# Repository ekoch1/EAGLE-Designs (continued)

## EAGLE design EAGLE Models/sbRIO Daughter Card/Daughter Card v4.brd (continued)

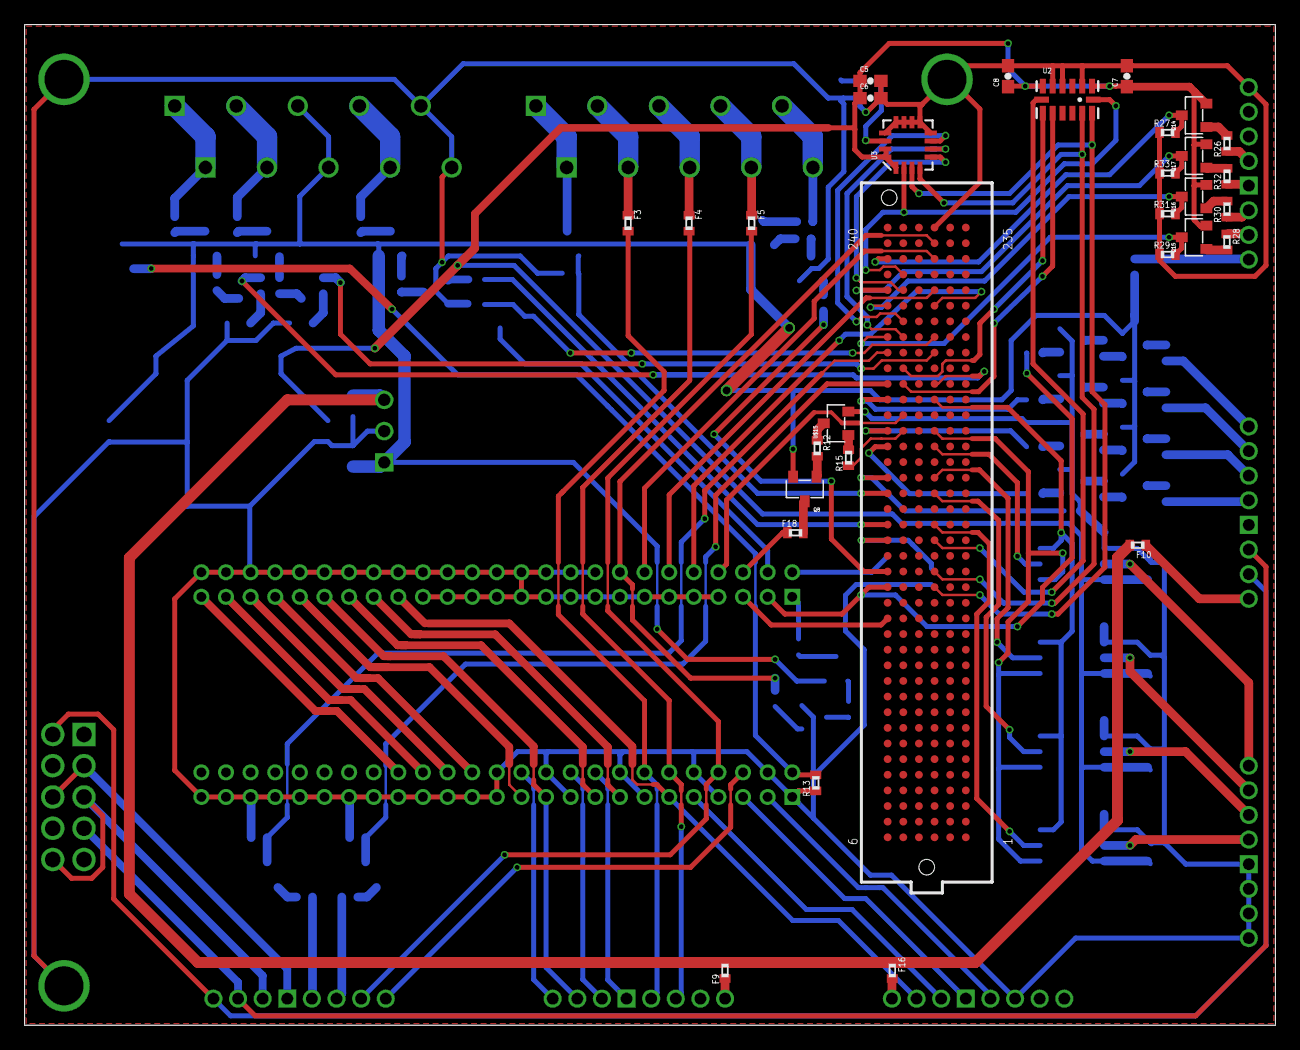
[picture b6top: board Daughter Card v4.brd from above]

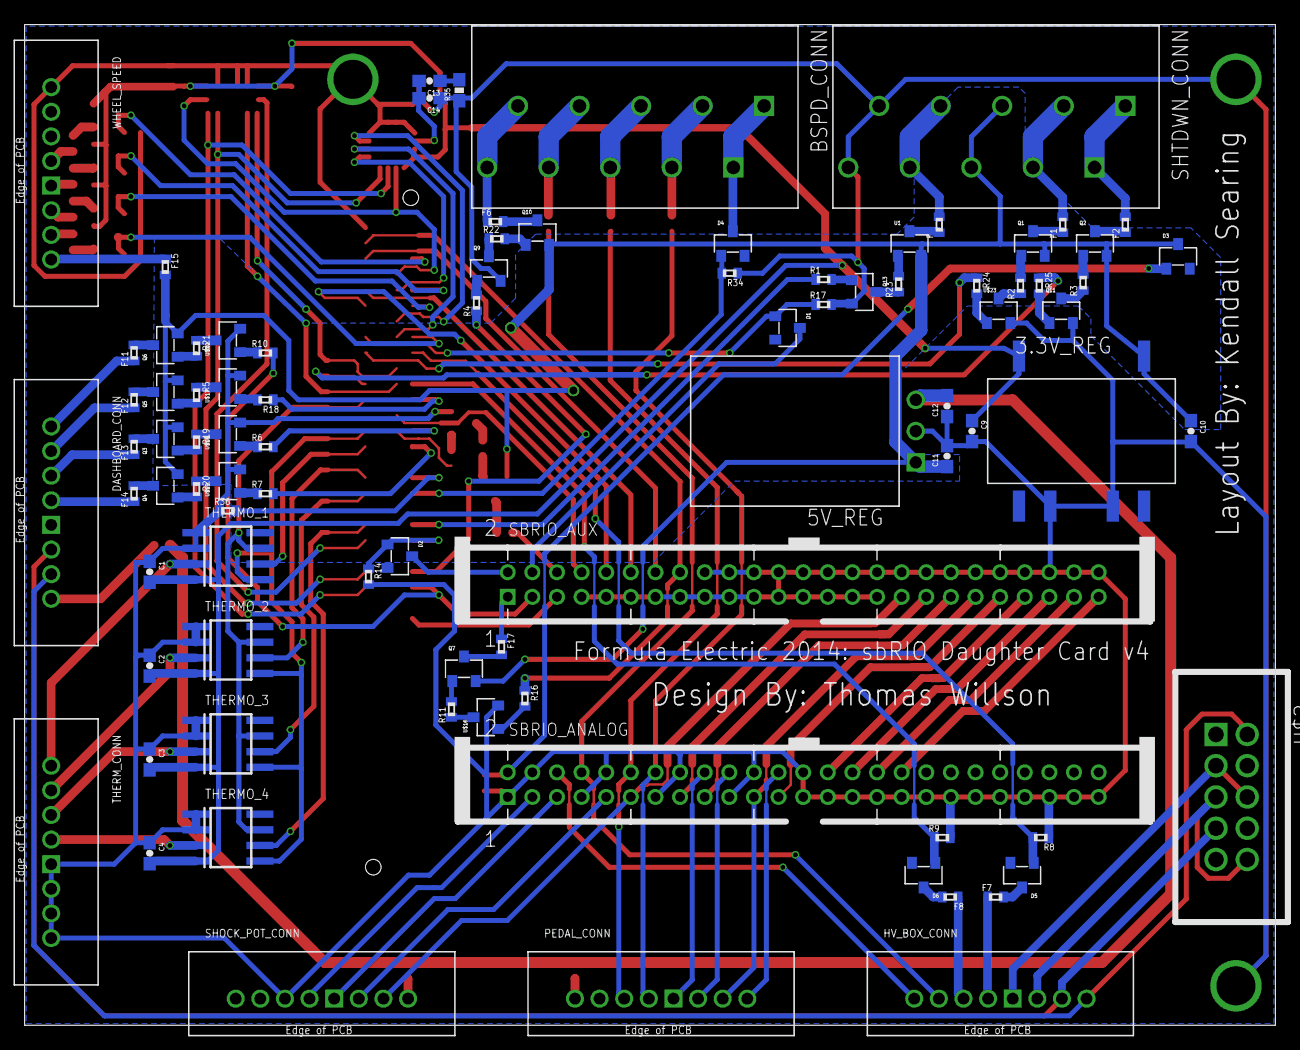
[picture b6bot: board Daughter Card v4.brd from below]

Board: 2 copper layers, 101.6 x 81.3 mm, 119 parts (88 on the bottom side), 146 nets.

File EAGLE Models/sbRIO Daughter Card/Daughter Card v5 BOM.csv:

"Part";"Value";"Device";"Package";"Description";"MF";"MPN";"OC_FARNELL";"OC_NEWARK";
"3.3V_REG";"V7803-1000";"V7803-1000";"V78XX-1000";"";"";"";"";"";
"5V_REG";"V78XX-1500";"V78XX-1500";"V78XX-1500R";"";"";"";"";"";
"ACCUMULATOR_CONN";"RJ45-6L21-S";"RJ45-6L21-S";"RJ45-SHIELD1";"RJ45 Low Profile Shield Type 2";"";"";"unknown";"unknown";
"AIO_PO_CONN";"2516-5";"2516-5";"PAK100/2500-5-16";"3M (TM) Pak 100 4-Wall Header";"";"D2516-5002-AR";"9838376";"12P7055";
"BSPD_CONN";"CONN_5";"CONN_5";"CONNECTOR_5";"";"";"";"";"";
"C5";".1uF";"CAP0603-CAP";"0603-CAP";"Capacitor";"";"";"";"";
"C6";"10uF";"CAP0603-CAP";"0603-CAP";"Capacitor";"";"";"";"";
"C7";".1uF";"CAP0603-CAP";"0603-CAP";"Capacitor";"";"";"";"";
"C8";"1uF";"CAP0603-CAP";"0603-CAP";"Capacitor";"";"";"";"";
"C9";"22uF";"CAP0603-CAP";"0603-CAP";"Capacitor";"";"";"";"";
"C10";"10uF";"CAP0603-CAP";"0603-CAP";"Capacitor";"";"";"";"";
"C11";"10uF";"CAP0603-CAP";"0603-CAP";"Capacitor";"";"";"";"";
"C12";"22uF";"CAP0603-CAP";"0603-CAP";"Capacitor";"";"";"";"";
"C13";"470nF";"CAP0603-CAP";"0603-CAP";"Capacitor";"";"";"";"";
"C14";"10nF";"CAP0603-CAP";"0603-CAP";"Capacitor";"";"";"";"";
"D1";"MMBZ5238B-7-F";"MMBZ5238B-7-F";"SOT-23-3";"Digikey: MMBZ5238B-FDICT-ND";"";"";"";"";
"D2";"MMBZ5238B-7-F";"MMBZ5238B-7-F";"SOT-23-3";"Digikey: MMBZ5238B-FDICT-ND";"";"";"";"";
"D3";"MMBZ5238B-7-F";"MMBZ5238B-7-F";"SOT-23-3";"Digikey: MMBZ5238B-FDICT-ND";"";"";"";"";
"D4";"MMBZ5238B-7-F";"MMBZ5238B-7-F";"SOT-23-3";"Digikey: MMBZ5238B-FDICT-ND";"";"";"";"";
"D5";"MMBZ5238B-7-F";"MMBZ5238B-7-F";"SOT-23-3";"Digikey: MMBZ5238B-FDICT-ND";"";"";"";"";
"D6";"MMBZ5238B-7-F";"MMBZ5238B-7-F";"SOT-23-3";"Digikey: MMBZ5238B-FDICT-ND";"";"";"";"";
"F1";"";"R-EU_R0402";"R0402";"RESISTOR, European symbol";"";"";"";"";
"F2";"";"R-EU_R0402";"R0402";"RESISTOR, European symbol";"";"";"";"";
"F3";"";"R-EU_R0402";"R0402";"RESISTOR, European symbol";"";"";"";"";
"F4";"";"R-EU_R0402";"R0402";"RESISTOR, European symbol";"";"";"";"";
"F5";"";"R-EU_R0402";"R0402";"RESISTOR, European symbol";"";"";"";"";
"F6";"";"R-EU_R0402";"R0402";"RESISTOR, European symbol";"";"";"";"";
"F7";"";"R-EU_R0402";"R0402";"RESISTOR, European symbol";"";"";"";"";
"F8";"";"R-EU_R0402";"R0402";"RESISTOR, European symbol";"";"";"";"";
"F9";"";"R-EU_R0402";"R0402";"RESISTOR, European symbol";"";"";"";"";
"F10";"";"R-EU_R0402";"R0402";"RESISTOR, European symbol";"";"";"";"";
"F14";"";"R-EU_R0402";"R0402";"RESISTOR, European symbol";"";"";"";"";
"F15";"";"R-EU_R0402";"R0402";"RESISTOR, European symbol";"";"";"";"";
"F16";"";"R-EU_R0402";"R0402";"RESISTOR, European symbol";"";"";"";"";
"F17";"";"R-EU_R0402";"R0402";"RESISTOR, European symbol";"";"";"";"";
"F18";"";"R-EU_R0402";"R0402";"RESISTOR, European symbol";"";"";"";"";
"F19";"";"R-EU_R0402";"R0402";"RESISTOR, European symbol";"";"";"";"";
"F20";"";"R-EU_R0402";"R0402";"RESISTOR, European symbol";"";"";"";"";
"F21";"";"R-EU_R0402";"R0402";"RESISTOR, European symbol";"";"";"";"";
"F22";"";"R-EU_R0402";"R0402";"RESISTOR, European symbol";"";"";"";"";
"IC1";"BTS716G";"BTS716G";"PG-DSO-20";"Smart High-Side Power Switch Four Channels: 4 x 140mOhm staus Feedback";"";"";"unknown";"unknown";
"IC2";"BTS716G";"BTS716G";"PG-DSO-20";"Smart High-Side Power Switch Four Channels: 4 x 140mOhm staus Feedback";"";"";"unknown";"unknown";
"IC3";"BTS716G";"BTS716G";"PG-DSO-20";"Smart High-Side Power Switch Four Channels: 4 x 140mOhm staus Feedback";"";"";"unknown";"unknown";
"Q7";"MMBT4403-7-F";"MMBT4403-7-F";"SOT-23-3";"";"";"";"";"";
"Q8";"MMBT4403-7-F";"MMBT4403-7-F";"SOT-23-3";"";"";"";"";"";
"R8";"10k";"R-US_R0402";"R0402";"RESISTOR, American symbol";"";"";"";"";
"R9";"10k";"R-US_R0402";"R0402";"RESISTOR, American symbol";"";"";"";"";
"R11";"4.7k";"R-US_R0402";"R0402";"RESISTOR, American symbol";"";"";"";"";
"R12";"4.7k";"R-US_R0402";"R0402";"RESISTOR, American symbol";"";"";"";"";
"R13";"10k";"R-US_R0402";"R0402";"RESISTOR, American symbol";"";"";"";"";
"R14";"10k";"R-US_R0402";"R0402";"RESISTOR, American symbol";"";"";"";"";
"R15";"4.7k";"R-US_R0402";"R0402";"RESISTOR, American symbol";"";"";"";"";
"R16";"4.7k";"R-US_R0402";"R0402";"RESISTOR, American symbol";"";"";"";"";
"R17";"10k";"R-US_R0402";"R0402";"RESISTOR, American symbol";"";"";"";"";
"R34";"10k";"R-US_R0402";"R0402";"RESISTOR, American symbol";"";"";"";"";
"R35";"10K";"RESISTOR0603-RES";"0603-RES";"Resistor";"";"";"";"";
"R36";"10k";"R-US_R0402";"R0402";"RESISTOR, American symbol";"";"";"";"";
"SBRIO_ANALOG";"SBRIO_MIO";"SBRIO_MIO";"SBRIO_J502_J503";"";"";"";"";"";
"SBRIO_AUX";"SBRIO_AUX";"SBRIO_AUX";"SBRIO_J502_J503";"An output for a lot of the extra pins on the sbRIO.";"";"";"";"";
"SHTDWN_CONN";"CONN_5";"CONN_5";"CONNECTOR_5";"";"";"";"";"";
"TUB_CONN";"2516-5";"2516-5";"PAK100/2500-5-16";"3M (TM) Pak 100 4-Wall Header";"";"D2516-5002-AR";"9838376";"12P7055";
"U$2";"SBRIO_W500";"SBRIO_W500";"SBRIO_W";"";"";"";"";"";
"U$3";"SBRIO_RMC";"SBRIO_RMC";"SEAM-40-XX.X-XX-06-X-A";"";"";"";"";"";
"U$15";"MMBT4401-7-F";"MMBT4401-7-F";"SOT-23-3";"";"";"";"";"";
"U$16";"MMBT4401-7-F";"MMBT4401-7-F";"SOT-23-3";"";"";"";"";"";
"U1";"";"TXB0104PWR";"TSSOP14";"4-Bit Bi-Directional Level Shifter";"";"";"";"";
"U2";"ADXL345";"ADXL345";"LGA14";"3-axis SPI/I2C 2/4/8/16g accelerometer";"";"";"";"";
"U3";"L3G4200D";"L3G4200D";"LGA16-4X4";"L3G4200D Three-axis, digital output gyroscope";"";"";"";"";
"X1";"5566-2";"5566-2";"5566-2";"Mini FIT connector 2 pol";"";"";"1822072";"unknown";
"X2";"";"FTOP-4";"FTOP-4";"AMP connector";"";"";"";"";

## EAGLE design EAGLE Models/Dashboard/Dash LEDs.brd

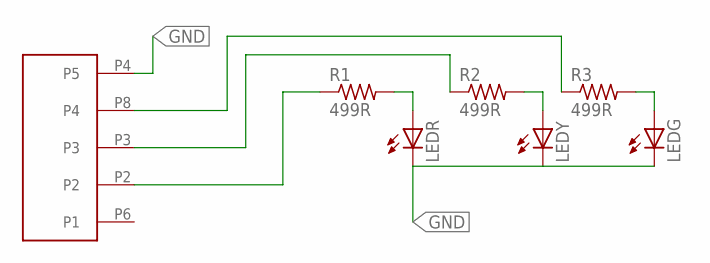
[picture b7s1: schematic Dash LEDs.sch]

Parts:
LEDG: LED5MM
LEDR: LED5MM
LEDY: LED5MM
R1, R2, R3: 499R; R0805
U$1: PICOLOCK

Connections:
DRV1: R1.1, U$1.P2
DRV2: R2.1, U$1.P3
DRV3: R3.1, U$1.P8 (P4)
GND: LEDG.K (C), LEDR.K (C), LEDY.K (C), U$1.P4 (P5)
unnamed: LEDR.A, R1.2
unnamed: LEDY.A, R2.2
unnamed: LEDG.A, R3.2

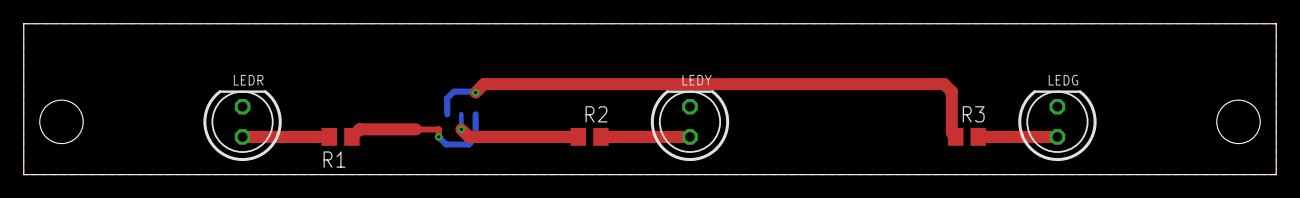
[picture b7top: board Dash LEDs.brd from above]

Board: 2 copper layers, 105.4 x 12.7 mm, 7 parts (1 on the bottom side), 7 nets.

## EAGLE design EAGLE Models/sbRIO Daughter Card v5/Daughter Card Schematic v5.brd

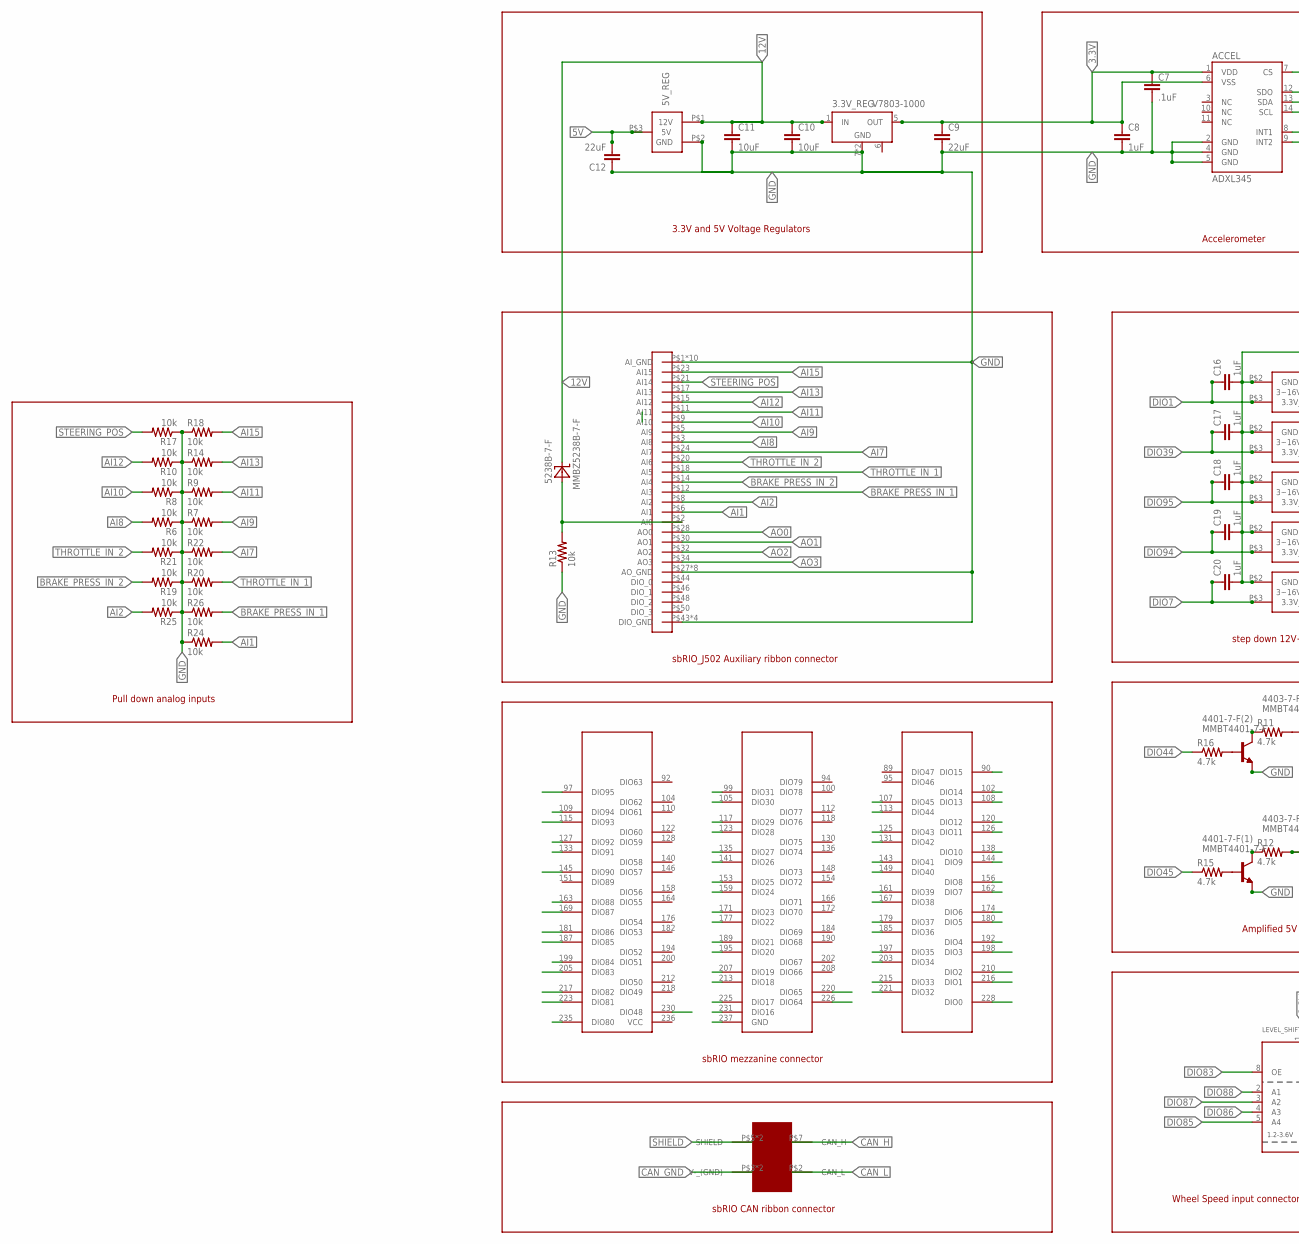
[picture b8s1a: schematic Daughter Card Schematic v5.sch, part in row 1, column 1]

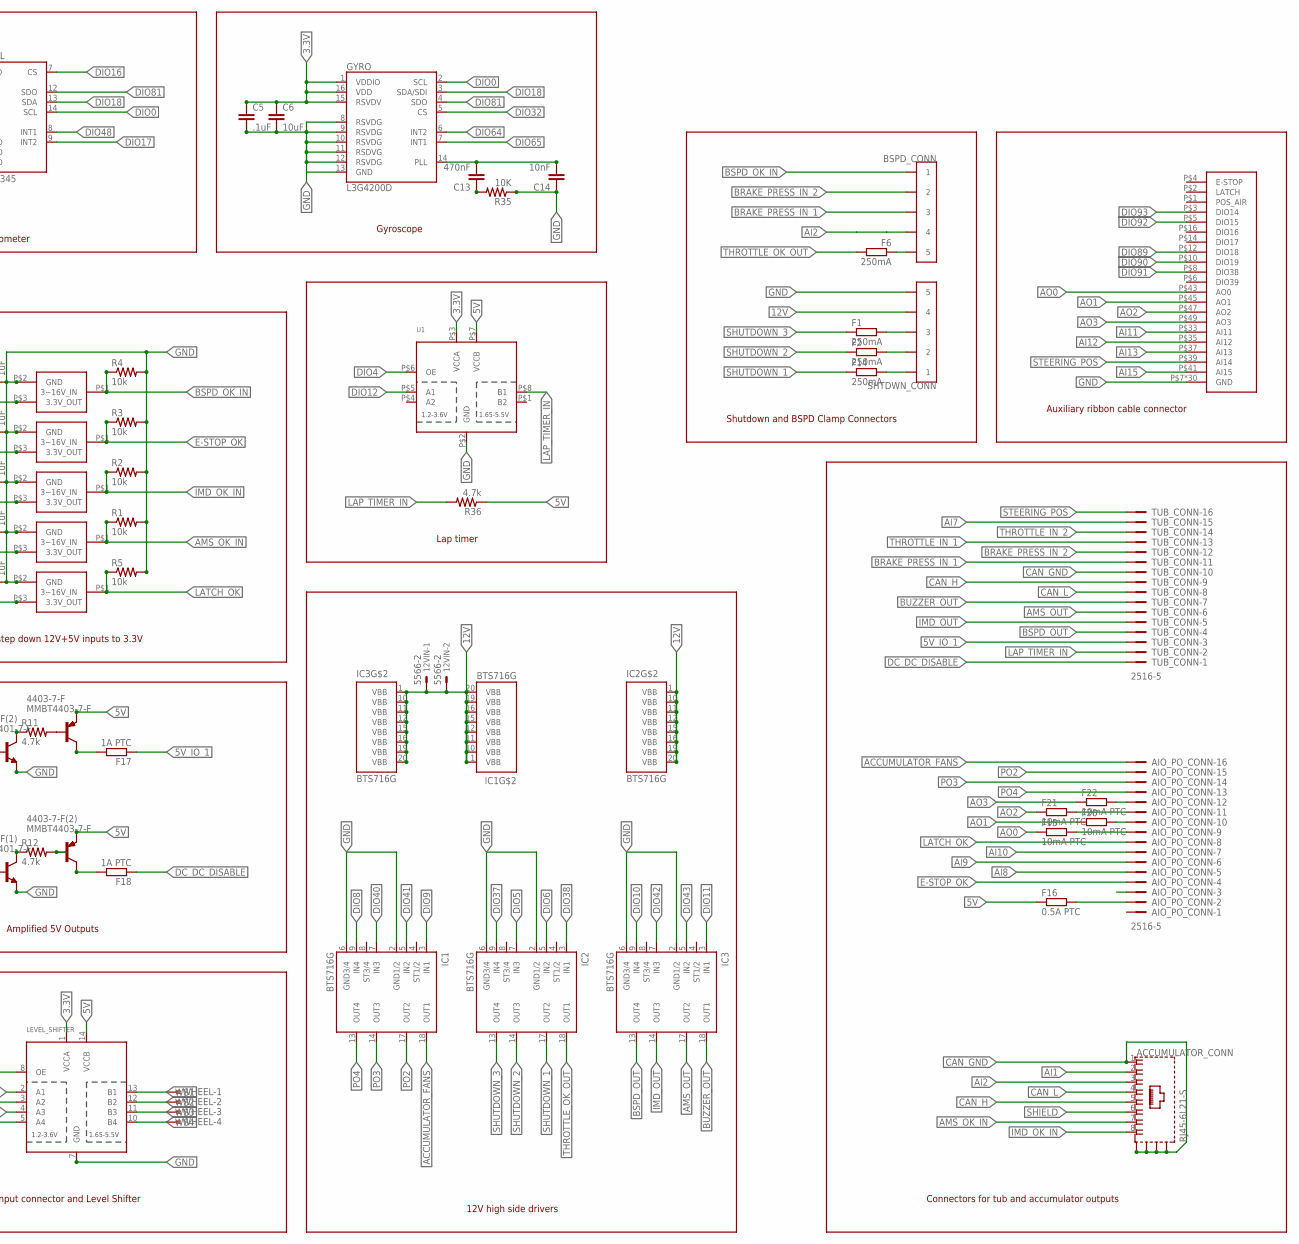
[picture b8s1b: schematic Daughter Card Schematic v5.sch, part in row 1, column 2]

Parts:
3.3V_REG: V7803-1000; V78XX-1000
5V_REG: V78XX-1500; V78XX-1500R
12VIN: 5566-2
4401-7-F(1), 4401-7-F(2): MMBT4401-7-F; SOT-23-3
4403-7-F, 4403-7-F(2): MMBT4403-7-F; SOT-23-3
5225-3.3M5-TR(5), 5525-3.3YM5-TR(1), 5525-3.3YM5-TR(2), 5525-3.3YM5-TR(3), 5525-3.3YM5-TR(4): MIC5225-3.3YM5-TR; SOT-23-3
5238B-7-F: MMBZ5238B-7-F; SOT-23-3
ACCEL: ADXL345; LGA14
ACCUMULATOR_CONN: RJ45-6L21-S; RJ45-SHIELD1
AIO_PO_CONN: 2516-5; PAK100/2500-5-16
BSPD_CONN: CONN_5; CONNECTOR_5
C5, C7: .1uF; 0603-CAP
C6, C10, C11: 10uF; 0603-CAP
C8, C16, C17, C18, C19, C20: 1uF; 0603-CAP
C9, C12: 22uF; 0603-CAP
C13: 470nF; 0603-CAP
C14: 10nF; 0603-CAP
F1, F2, F6, F14: 250mA; R0603
F15, F20, F21, F22: 10mA PTC; R0402
F16: 0.5A PTC; R0603
F17, F18: 1A PTC; R0603
GYRO: L3G4200D; LGA16-4X4
IC1, IC2, IC3: BTS716G; PG-DSO-20
LEVEL_SHIFTER: TXB0104PWR; TSSOP14
R1, R2, R3, R4, R5, R6, R7, R8, R9, R10, R13, R14, R17, R18, R19, R20, R21, R22, R24, R25, R26: 10k; R0402
R11, R12, R15, R16, R36: 4.7k; R0402
R35: 10K; 0603-RES
SBRIO_ANALOG: SBRIO_MIO; SBRIO_J502_J503
SBRIO_AUX: SBRIO_AUX; SBRIO_J502_J503
SBRIO_CAN: SBRIO_W500; SBRIO_W
SBRIO_MEZZANINE: SBRIO_RMC; SEAM-40-XX.X-XX-06-X-A
SHTDWN_CONN: CONN_5; CONNECTOR_5
TUB_CONN: 2516-5; PAK100/2500-5-16
U1: TXS0102; VFSOP-8
WHEEL: FTOP-4

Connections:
3.3V: 3.3V_REG.5 (OUT), ACCEL.1 (VDD), ACCEL.6 (VSS), C5.1, C6.1, C7.1, C8.1, C9.1, GYRO.1 (VDDIO), GYRO.15 (RSVDV), GYRO.16 (VDD), LEVEL_SHIFTER.1 (VCCA), U1.P$3 (VCCA)
5V: 5V_REG.P$3 (5V), 4403-7-F.P$3 (E), 4403-7-F(2).P$3 (E), C12.2, F16.1, LEVEL_SHIFTER.14 (VCCB), R36.1, U1.P$7 (VCCB)
5V_IO_1: F17.1, TUB_CONN.3
12V: 3.3V_REG.1 (IN), 5V_REG.P$1 (12V), 12VIN.1, 12VIN.2, 5238B-7-F.P$1 (C), C10.1, C11.1, IC1.1 (VBB), IC1.10 (VBB), IC1.11 (VBB), IC1.12 (VBB), IC1.15 (VBB), IC1.16 (VBB), IC1.19 (VBB), IC1.20 (VBB), IC2.1 (VBB), IC2.10 (VBB), IC2.11 (VBB), IC2.12 (VBB), IC2.15 (VBB), IC2.16 (VBB), IC2.19 (VBB), IC2.20 (VBB), IC3.1 (VBB), IC3.10 (VBB), IC3.11 (VBB), IC3.12 (VBB), IC3.15 (VBB), IC3.16 (VBB), IC3.19 (VBB), IC3.20 (VBB), SHTDWN_CONN.7 (4), SHTDWN_CONN.8 (4)
ACCUMULATOR_FANS: AIO_PO_CONN.16, IC1.18 (OUT1)
AI1: ACCUMULATOR_CONN.2, R24.2, SBRIO_ANALOG.P$6 (AI1)
AI2: ACCUMULATOR_CONN.3, BSPD_CONN.7 (4), BSPD_CONN.8 (4), R25.2, SBRIO_ANALOG.P$8 (AI2)
AI7: R22.2, SBRIO_ANALOG.P$24 (AI7), TUB_CONN.15
AI8: AIO_PO_CONN.5, R6.2, SBRIO_ANALOG.P$3 (AI8)
AI9: AIO_PO_CONN.6, R7.2, SBRIO_ANALOG.P$5 (AI9)
AI10: AIO_PO_CONN.7, R8.2, SBRIO_ANALOG.P$9 (AI10)
AI11: R9.2, SBRIO_ANALOG.P$11 (AI11), SBRIO_AUX.P$33 (AI11)
AI12: R10.2, SBRIO_ANALOG.P$15 (AI12), SBRIO_AUX.P$35 (AI12)
AI13: R14.2, SBRIO_ANALOG.P$17 (AI13), SBRIO_AUX.P$37 (AI13)
AI15: R18.2, SBRIO_ANALOG.P$23 (AI15), SBRIO_AUX.P$41 (AI15)
AMS_OK_IN: 5525-3.3YM5-TR(1).P$1 (3~16V_IN), ACCUMULATOR_CONN.7, R1.1
AMS_OUT: IC3.17 (OUT2), TUB_CONN.6
AO0: F15.1, SBRIO_ANALOG.P$28 (AO0), SBRIO_AUX.P$43 (AO0)
AO1: F20.1, SBRIO_ANALOG.P$30 (AO1), SBRIO_AUX.P$45 (AO1)
AO2: F21.1, SBRIO_ANALOG.P$32 (AO2), SBRIO_AUX.P$47 (AO2)
AO3: F22.1, SBRIO_ANALOG.P$34 (AO3), SBRIO_AUX.P$49 (AO3)
BRAKE_PRESS_IN_1: BSPD_CONN.5 (3), BSPD_CONN.6 (3), R26.2, SBRIO_ANALOG.P$12 (AI3), TUB_CONN.11
BRAKE_PRESS_IN_2: BSPD_CONN.3 (2), BSPD_CONN.4 (2), R19.2, SBRIO_ANALOG.P$14 (AI4), TUB_CONN.12
BSPD_OK_IN: 5525-3.3YM5-TR(3).P$1 (3~16V_IN), BSPD_CONN.1, BSPD_CONN.2 (1), R4.1
BSPD_OUT: IC3.13 (OUT4), TUB_CONN.4
BUZZER_OUT: IC3.18 (OUT1), TUB_CONN.7
CAN_GND: ACCUMULATOR_CONN.1, ACCUMULATOR_CONN.S1 (S), ACCUMULATOR_CONN.S2 (S), ACCUMULATOR_CONN.S3 (S), ACCUMULATOR_CONN.S4 (S), SBRIO_CAN.P$3 (V-_(GND)), SBRIO_CAN.P$6 (V-_(GND)), TUB_CONN.10
CAN_H: ACCUMULATOR_CONN.5, SBRIO_CAN.P$7 (CAN_H), TUB_CONN.9
CAN_L: ACCUMULATOR_CONN.4, SBRIO_CAN.P$2 (CAN_L), TUB_CONN.8
DC_DC_DISABLE: F18.1, TUB_CONN.1
DIO0: ACCEL.14 (SCL), GYRO.2 (SCL), SBRIO_MEZZANINE.228 (DIO0)
DIO1: 5525-3.3YM5-TR(3).P$3 (3.3V_OUT), C16.1, SBRIO_MEZZANINE.216 (DIO1)
DIO2: SBRIO_MEZZANINE.210 (DIO2)
DIO3: SBRIO_MEZZANINE.198 (DIO3)
DIO4: SBRIO_MEZZANINE.192 (DIO4), U1.P$6 (OE)
DIO5: IC2.7 (IN3), SBRIO_MEZZANINE.180 (DIO5)
DIO6: IC2.5 (IN2), SBRIO_MEZZANINE.174 (DIO6)
DIO7: 5525-3.3YM5-TR(2).P$3 (3.3V_OUT), C20.1, SBRIO_MEZZANINE.162 (DIO7)
DIO8: IC1.9 (IN4), SBRIO_MEZZANINE.156 (DIO8)
DIO9: IC1.3 (IN1), SBRIO_MEZZANINE.144 (DIO9)
DIO10: IC3.9 (IN4), SBRIO_MEZZANINE.138 (DIO10)
DIO11: IC3.3 (IN1), SBRIO_MEZZANINE.126 (DIO11)
DIO12: SBRIO_MEZZANINE.120 (DIO12), U1.P$5 (A1)
DIO13: SBRIO_MEZZANINE.108 (DIO13)
DIO14: SBRIO_MEZZANINE.102 (DIO14)
DIO15: SBRIO_MEZZANINE.90 (DIO15)
DIO16: ACCEL.7 (CS), SBRIO_MEZZANINE.231 (DIO16)
DIO17: ACCEL.9 (INT2), SBRIO_MEZZANINE.225 (DIO17)
DIO18: ACCEL.13 (SDA), GYRO.3 (SDA/SDI), SBRIO_MEZZANINE.213 (DIO18)
DIO19: SBRIO_MEZZANINE.207 (DIO19)
DIO20: SBRIO_MEZZANINE.195 (DIO20)
DIO21: SBRIO_MEZZANINE.189 (DIO21)
DIO22: SBRIO_MEZZANINE.177 (DIO22)
DIO23: SBRIO_MEZZANINE.171 (DIO23)
DIO24: SBRIO_MEZZANINE.159 (DIO24)
DIO25: SBRIO_MEZZANINE.153 (DIO25)
DIO26: SBRIO_MEZZANINE.141 (DIO26)
DIO27: SBRIO_MEZZANINE.135 (DIO27)
DIO28: SBRIO_MEZZANINE.123 (DIO28)
DIO29: SBRIO_MEZZANINE.117 (DIO29)
DIO30: SBRIO_MEZZANINE.105 (DIO30)
DIO31: SBRIO_MEZZANINE.99 (DIO31)
DIO32: GYRO.5 (CS), SBRIO_MEZZANINE.221 (DIO32)
DIO33: SBRIO_MEZZANINE.215 (DIO33)
DIO34: SBRIO_MEZZANINE.203 (DIO34)
DIO35: SBRIO_MEZZANINE.197 (DIO35)
DIO36: SBRIO_MEZZANINE.185 (DIO36)
DIO37: IC2.9 (IN4), SBRIO_MEZZANINE.179 (DIO37)
DIO38: IC2.3 (IN1), SBRIO_MEZZANINE.167 (DIO38)
DIO39: 5525-3.3YM5-TR(4).P$3 (3.3V_OUT), C17.1, SBRIO_MEZZANINE.161 (DIO39)
DIO40: IC1.7 (IN3), SBRIO_MEZZANINE.149 (DIO40)
DIO41: IC1.5 (IN2), SBRIO_MEZZANINE.143 (DIO41)
DIO42: IC3.7 (IN3), SBRIO_MEZZANINE.131 (DIO42)
DIO43: IC3.5 (IN2), SBRIO_MEZZANINE.125 (DIO43)
DIO44: R16.1, SBRIO_MEZZANINE.113 (DIO44)
DIO45: R15.1, SBRIO_MEZZANINE.107 (DIO45)
DIO48: ACCEL.8 (INT1), SBRIO_MEZZANINE.230 (DIO48)
DIO64: GYRO.6 (INT2), SBRIO_MEZZANINE.226 (DIO64)
DIO65: GYRO.7 (INT1), SBRIO_MEZZANINE.220 (DIO65)
DIO80: SBRIO_MEZZANINE.235 (DIO80)
DIO81: ACCEL.12 (SDO), GYRO.4 (SDO), SBRIO_MEZZANINE.223 (DIO81)
DIO82: SBRIO_MEZZANINE.217 (DIO82)
DIO83: LEVEL_SHIFTER.8 (OE), SBRIO_MEZZANINE.205 (DIO83)
DIO84: SBRIO_MEZZANINE.199 (DIO84)
DIO85: LEVEL_SHIFTER.5 (A4), SBRIO_MEZZANINE.187 (DIO85)
DIO86: LEVEL_SHIFTER.4 (A3), SBRIO_MEZZANINE.181 (DIO86)
DIO87: LEVEL_SHIFTER.3 (A2), SBRIO_MEZZANINE.169 (DIO87)
DIO88: LEVEL_SHIFTER.2 (A1), SBRIO_MEZZANINE.163 (DIO88)
DIO89: SBRIO_AUX.P$12 (DIO18)
DIO90: SBRIO_AUX.P$10 (DIO19), SBRIO_MEZZANINE.145 (DIO90)
DIO91: SBRIO_AUX.P$8 (DIO38), SBRIO_MEZZANINE.133 (DIO91)
DIO92: SBRIO_AUX.P$5 (DIO15), SBRIO_MEZZANINE.127 (DIO92)
DIO93: SBRIO_AUX.P$3 (DIO14), SBRIO_MEZZANINE.115 (DIO93)
DIO94: 5525-3.3YM5-TR(1).P$3 (3.3V_OUT), C19.1, SBRIO_MEZZANINE.109 (DIO94)
DIO95: 5225-3.3M5-TR(5).P$3 (3.3V_OUT), C18.1, SBRIO_MEZZANINE.97 (DIO95)
E-STOP_OK: 5525-3.3YM5-TR(4).P$1 (3~16V_IN), AIO_PO_CONN.4, R3.1
GND: 3.3V_REG.7 (GND), 3.3V_REG.9 (GND), 5V_REG.P$2 (GND), 4401-7-F(1).P$3 (E), 4401-7-F(2).P$3 (E), 5225-3.3M5-TR(5).P$2 (GND), 5525-3.3YM5-TR(1).P$2 (GND), 5525-3.3YM5-TR(2).P$2 (GND), 5525-3.3YM5-TR(3).P$2 (GND), 5525-3.3YM5-TR(4).P$2 (GND), ACCEL.2 (GND), ACCEL.4 (GND), ACCEL.5 (GND), C5.2, C6.2, C7.2, C8.2, C9.2, C10.2, C11.2, C12.1, C14.1, C16.2, C17.2, C18.2, C19.2, C20.2, GYRO.8 (RSVDG), GYRO.9 (RSVDG), GYRO.10 (RSVDG), GYRO.11 (RSDVG), GYRO.12 (RSVDG), GYRO.13 (GND), IC1.2 (GND1/2), IC1.6 (GND3/4), IC2.2 (GND1/2), IC2.6 (GND3/4), IC3.2 (GND1/2), IC3.6 (GND3/4), LEVEL_SHIFTER.7 (GND), R1.2, R2.2, R3.2, R4.2, R5.2, R6.1, R7.1, R8.1, R9.1, R10.1, R13.1, R14.1, R17.1, R18.1, R19.1, R20.1, R21.1, R22.1, R24.1, R25.1, R26.1, R35.1, SBRIO_ANALOG.P$1 (AI_GND), SBRIO_ANALOG.P$4 (AI_GND), SBRIO_ANALOG.P$7 (AI_GND), SBRIO_ANALOG.P$10 (AI_GND), SBRIO_ANALOG.P$13 (AI_GND), SBRIO_ANALOG.P$16 (AI_GND), SBRIO_ANALOG.P$19 (AI_GND), SBRIO_ANALOG.P$22 (AI_GND), SBRIO_ANALOG.P$25 (AI_GND), SBRIO_ANALOG.P$26 (AI_GND), SBRIO_ANALOG.P$27 (AO_GND), SBRIO_ANALOG.P$29 (AO_GND), SBRIO_ANALOG.P$31 (AO_GND), SBRIO_ANALOG.P$33 (AO_GND), SBRIO_ANALOG.P$35 (AO_GND), SBRIO_ANALOG.P$37 (AO_GND), SBRIO_ANALOG.P$39 (AO_GND), SBRIO_ANALOG.P$41 (AO_GND), SBRIO_ANALOG.P$43 (DIO_GND), SBRIO_ANALOG.P$45 (DIO_GND), SBRIO_ANALOG.P$47 (DIO_GND), SBRIO_ANALOG.P$49 (DIO_GND), SBRIO_AUX.P$7 (GND), SBRIO_AUX.P$9 (GND), SBRIO_AUX.P$11 (GND), SBRIO_AUX.P$13 (GND), SBRIO_AUX.P$15 (GND), SBRIO_AUX.P$17 (GND), SBRIO_AUX.P$18 (GND), SBRIO_AUX.P$19 (GND), SBRIO_AUX.P$20 (GND), SBRIO_AUX.P$21 (GND), SBRIO_AUX.P$22 (GND), SBRIO_AUX.P$23 (GND), SBRIO_AUX.P$24 (GND), SBRIO_AUX.P$25 (GND), SBRIO_AUX.P$26 (GND), SBRIO_AUX.P$27 (GND), SBRIO_AUX.P$28 (GND), SBRIO_AUX.P$29 (GND), SBRIO_AUX.P$30 (GND), SBRIO_AUX.P$31 (GND), SBRIO_AUX.P$32 (GND), SBRIO_AUX.P$34 (GND), SBRIO_AUX.P$36 (GND), SBRIO_AUX.P$38 (GND), SBRIO_AUX.P$40 (GND), SBRIO_AUX.P$42 (GND), SBRIO_AUX.P$44 (GND), SBRIO_AUX.P$46 (GND), SBRIO_AUX.P$48 (GND), SBRIO_AUX.P$50 (GND), SBRIO_MEZZANINE.237 (GND), SHTDWN_CONN.9 (5), SHTDWN_CONN.10 (5), U1.P$2 (GND)
IMD_OK_IN: 5225-3.3M5-TR(5).P$1 (3~16V_IN), ACCUMULATOR_CONN.8, R2.1
IMD_OUT: IC3.14 (OUT3), TUB_CONN.5
LAP_TIMER_IN: R36.2, TUB_CONN.2, U1.P$8 (B1)
LATCH_OK: 5525-3.3YM5-TR(2).P$1 (3~16V_IN), AIO_PO_CONN.8, R5.1
unnamed: AIO_PO_CONN.9, F15.2
unnamed: 5238B-7-F.P$2 (A), R13.2, SBRIO_ANALOG.P$2 (AI0)
unnamed: AIO_PO_CONN.10, F20.2
unnamed: AIO_PO_CONN.11, F21.2
unnamed: AIO_PO_CONN.12, F22.2
unnamed: F1.2, SHTDWN_CONN.5 (3), SHTDWN_CONN.6 (3)
unnamed: F2.2, SHTDWN_CONN.3 (2), SHTDWN_CONN.4 (2)
unnamed: F14.2, SHTDWN_CONN.1, SHTDWN_CONN.2 (1)
unnamed: AIO_PO_CONN.2, F16.2
unnamed: C13.2, C14.2, GYRO.14 (PLL)
unnamed: C13.1, R35.2
unnamed: BSPD_CONN.9 (5), BSPD_CONN.10 (5), F6.1
unnamed: 4403-7-F.P$2 (B), R11.2
unnamed: 4403-7-F.P$1 (C), F17.2
unnamed: 4403-7-F(2).P$1 (C), F18.2
unnamed: 4403-7-F(2).P$2 (B), R12.2
unnamed: 4401-7-F(1).P$2 (B), R15.2
unnamed: 4401-7-F(1).P$1 (C), R12.1
unnamed: 4401-7-F(2).P$2 (B), R16.2
unnamed: 4401-7-F(2).P$1 (C), R11.1
PO2: AIO_PO_CONN.15, IC1.17 (OUT2)
PO3: AIO_PO_CONN.14, IC1.14 (OUT3)
PO4: AIO_PO_CONN.13, IC1.13 (OUT4)
SHIELD: ACCUMULATOR_CONN.6, SBRIO_CAN.P$5 (SHIELD), SBRIO_CAN.P$10 (SHIELD)
SHUTDOWN_1: F14.1, IC2.17 (OUT2)
SHUTDOWN_2: F2.1, IC2.14 (OUT3)
SHUTDOWN_3: F1.1, IC2.13 (OUT4)
STEERING_POS: R17.2, SBRIO_ANALOG.P$21 (AI14), SBRIO_AUX.P$39 (AI14), TUB_CONN.16
THROTTLE_IN_1: R20.2, SBRIO_ANALOG.P$18 (AI5), TUB_CONN.13
THROTTLE_IN_2: R21.2, SBRIO_ANALOG.P$20 (AI6), TUB_CONN.14
THROTTLE_OK_OUT: F6.2, IC2.18 (OUT1)
VCC: SBRIO_MEZZANINE.236 (VCC)
WS1: LEVEL_SHIFTER.13 (B1), WHEEL.1
WS2: LEVEL_SHIFTER.12 (B2), WHEEL.2
WS3: LEVEL_SHIFTER.11 (B3), WHEEL.3
WS4: LEVEL_SHIFTER.10 (B4), WHEEL.4

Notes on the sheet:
step down 12V+5V inputs to 3.3V
Auxiliary ribbon cable connector
Amplified 5V Outputs
sbRIO CAN ribbon connector
sbRIO mezzanine connector
sbRIO_J502 Auxiliary ribbon connector
Gyroscope
3.3V and 5V Voltage Regulators
Accelerometer
Wheel Speed input connector and Level Shifter
Shutdown and BSPD Clamp Connectors
12V high side drivers
Lap timer
Connectors for tub and accumulator outputs
Pull down analog inputs

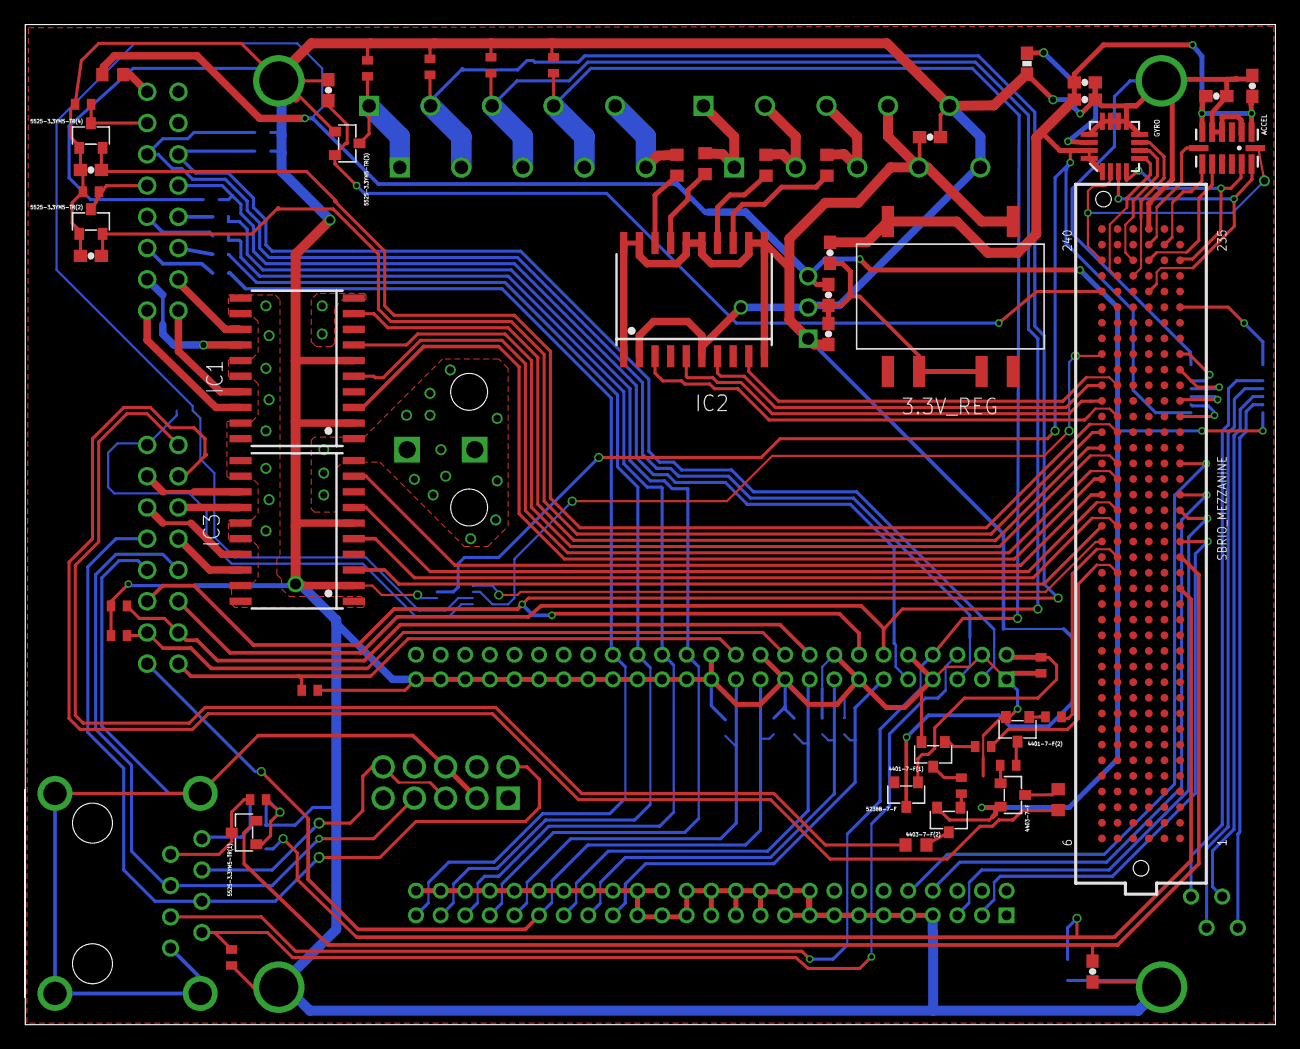
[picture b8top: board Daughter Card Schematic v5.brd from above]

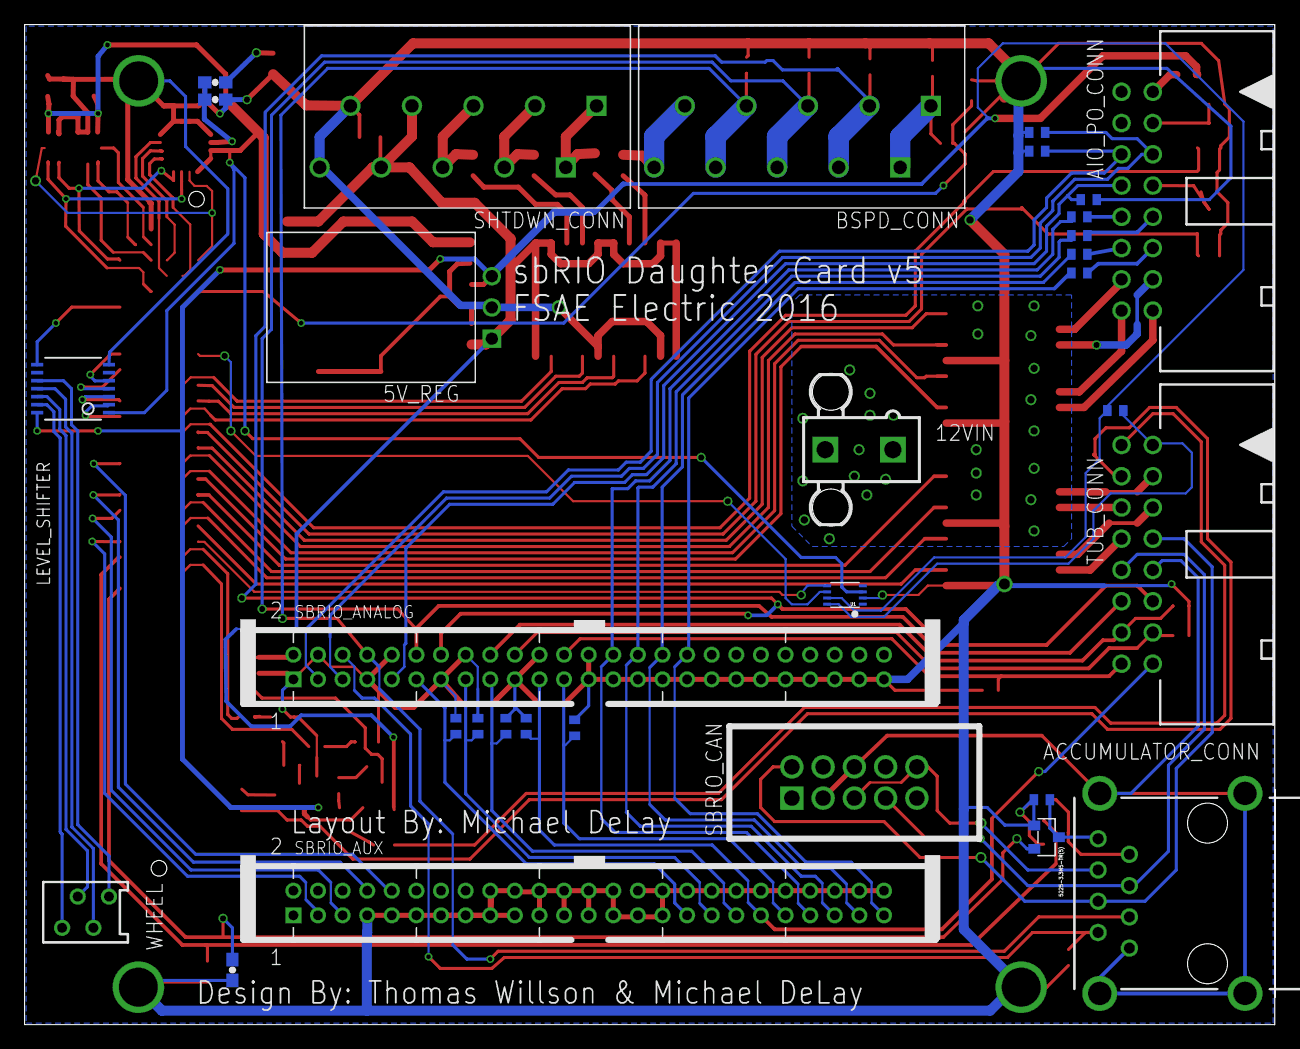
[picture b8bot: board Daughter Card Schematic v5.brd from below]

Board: 2 copper layers, 101.6 x 81.3 mm, 83 parts (31 on the bottom side), 110 nets.

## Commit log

2015-10-22 Initial Import
2015-10-22 Add gitignore and remove ignored files.
2015-10-22 Actually remove ignored files.
2015-10-22 Add reference dot for pin 1.
2015-10-22 Add pin 1 dot for cypress capsense chip.
2015-11-11 Changed HV board for putting in line with MC
    Integrated Discharge and TSAL circuit into one smaller board to put in a
    box in line with the motor controller.
2015-11-11 Revising Daughter Card
    stuff
2016-01-11 making daughter card revisions
2016-01-12 made many changes
2016-01-23 did things
2016-01-23 cleaned up silkscreen
2016-01-23 fixed broken board
2016-02-02 Changed daughter card stuff
2016-02-02 stuff
2016-02-02 Committed daughter card before autorouting
2016-02-02 fixed more traces
2016-02-02 fixed four outputs not connected in schematic
2016-02-02 did more things
2016-02-02 fixed traces that were unnecessary
2016-02-02 Made mezzanine connector have all pins connected
    connected DIO 40-95 to schematic and components so that one can choose
    better pin locations
2016-02-02 made daughter card amplifiers all based off of ICs
2016-02-02 more daughter card work
2016-02-02 made more changes to daughter card
2016-02-03 more daughter card revisions
2016-02-03 FINISHED DAUGHTER CARD LAYOUT
    haven't run DRC yet
2016-02-03 Routed extra DIO, because it was easy
2016-02-09 fixing drc errors
2016-02-10 Added pours and molex connector for amplified 12V
2016-02-10 Made layout pass DRC
    also added level shifted inputs for wheel speeds
2016-02-10 approved some ERC "errors"
2016-02-10 Added values for fuses
    also rerouted a trace which was unnecesarily long
2016-02-11 PTC fuses dont exisist in 0402, made all fuses 0603 instead
2016-02-11 some of the 0603 PTC fuses were not possible to lay on board well
    replaced with normal fuses
2016-02-13 changed step-down diodes into linear regulators
    also made schematic far more readable, and removed some unnecessary
    outputs on TUB_CONN
2016-02-13 indermediate commit during layout
2016-02-13 Made board pass DRC
2016-02-13 Fixed most of the issues with the daughter card
2016-02-13 Extended QFN leads
2016-02-13 Began preparing silkscreens for ordering
2016-02-13 Fixed silkscreen
2016-02-13 Fix small routing issue on ground connection of aux ribbon connector.
2016-02-13 Add lock files to gitignore.
2016-02-13 Correct spelling of my name.
2016-02-14 started adding pulldowns
2016-02-14 Fixed issues #6 and #7
2016-02-16 Add DRV8711 Stepper Motor Controller IC to library.
2016-02-16 Add Cal Poly Racing logo and clean up text.
2016-02-16 Intermediary commit with gerber files for daughter card.
    Gerber files are not yet fully verified.
2016-02-16 Final Gerber files for 2016 Daughter Card Order 1.
2016-02-17 Fix gerber file move.
2016-02-17 Add CSD18531Q5A to Texas Instruments library.
    Also adds SON5x6 & SON3x3 packages.
2016-02-22 Disable thermals for SON5x6 heat pad.
2016-02-22 Remove unnecessary feet in SON5x6.
2016-02-22 Better gate pad layout for SON5x6.
2016-02-22 Better source pad layout for SON5x6.
2016-02-22 No thermals on PowerPad.
2016-02-23 Move PC Power connector name to correct layer.
2016-02-23 Add updated OshPark CAM job.
2016-03-04 Add OSHPark 4 layer DRU.
2016-03-05 More repository cleanup.
2016-03-05 Cleanup BSPD Files.
2016-03-16 Add digilent library
2016-03-16 Fix package for CSD18531Q5A.
2016-03-16 Fix TI library merge.
    New part CSD18531Q5A had been lost in merge.
2016-04-10 fixed drills
2016-04-10 Fixed problem with AIL
    Zener was too small and board was not fused
2016-04-10 Add DRV8711 back to library after being deleted in the merge.
2016-04-11 Add keepout region under MOSFET to avoid shorting.
